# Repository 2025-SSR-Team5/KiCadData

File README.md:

# KiCadData

## Control Circuit<br>
- A面<br>
<br>

- B面<br>

連結した図
<br>

## Emergency Circuit<br>
動作電圧：7.8V以上（実測値）

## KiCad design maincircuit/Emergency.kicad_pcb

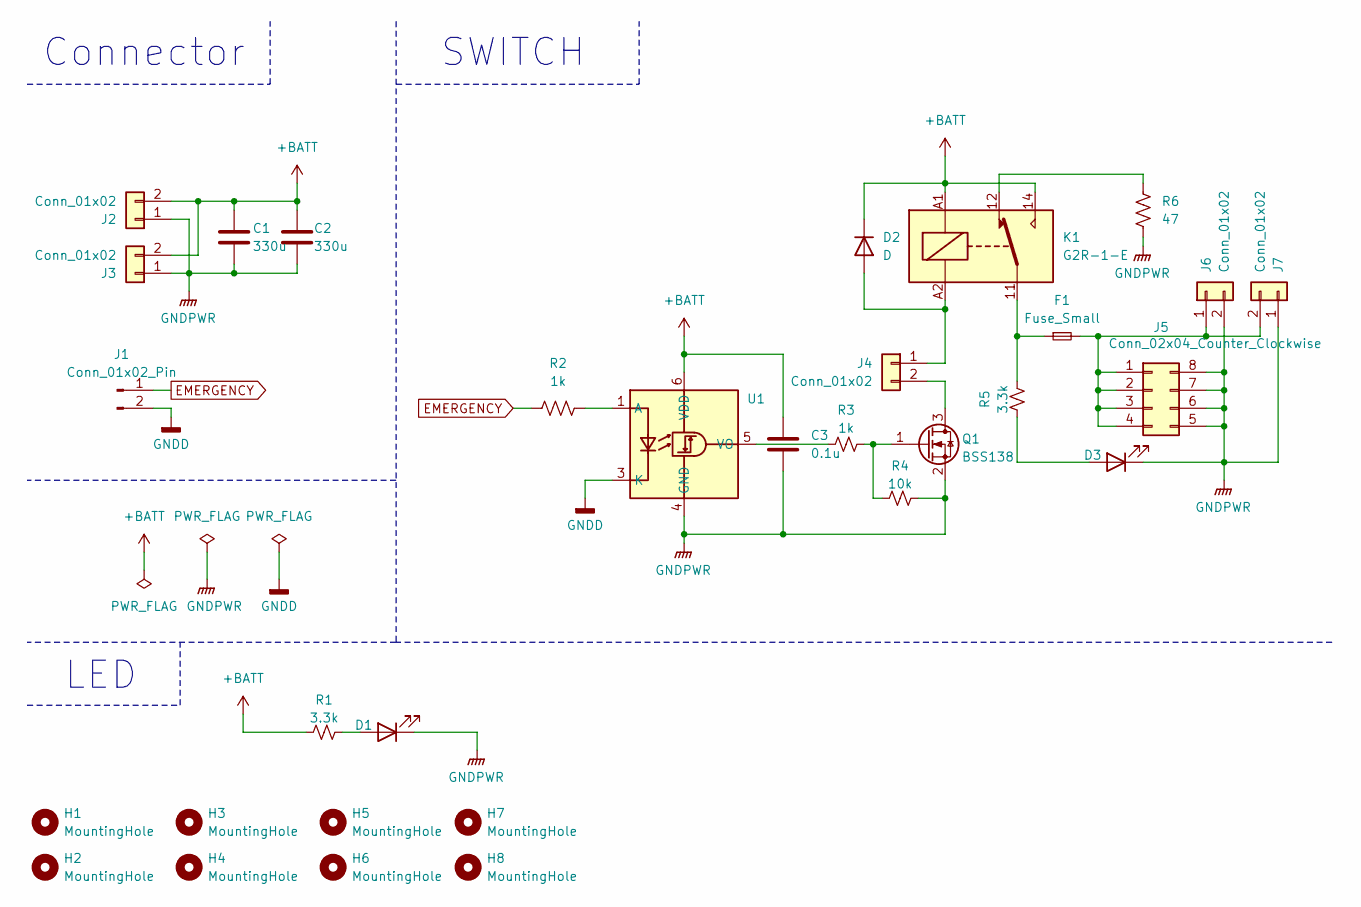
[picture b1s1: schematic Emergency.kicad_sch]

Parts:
C1, C2: 330u; CP_Elec_10x10
C3: 0.1u; C_0603_1608Metric_Pad1.08x0.95mm_HandSolder
D1, D3: LED; LED_0603_1608Metric
D2: D; D_DO-201AD_P15.24mm_Horizontal
F1: Fuse_Small; FUC-04
H1, H2, H3, H4, H5, H6, H7, H8: MountingHole; MountingHole_3.2mm_M3
J1: Conn_01x02_Pin; PinSocket_1x02_P2.54mm_Vertical
J2: Conn_01x02; AMASS_XT60PW-M_1x02_P7.20mm_Horizontal
J3, J7: Conn_01x02; AMASS_XT60PW-F_1x02_P7.20mm_Horizontal
J4, J6: Conn_01x02; JST_XH_B2B-XH-A_1x02_P2.50mm_Vertical
J5: Conn_02x04_Counter_Clockwise; PinSocket_2x04_P2.54mm_Vertical
K1: G2R-1-E
Q1: BSS138; SOT-23
R1, R5: 3.3k; R_0603_1608Metric_Pad0.98x0.95mm_HandSolder
R2, R3: 1k; R_0603_1608Metric_Pad0.98x0.95mm_HandSolder
R4: 10k; R_0603_1608Metric_Pad0.98x0.95mm_HandSolder
R6: 47; R_Axial_DIN0614_L14.3mm_D5.7mm_P20.32mm_Horizontal
U1: SO-5-6_4.55x3.7mm_P1.27mm

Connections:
+BATT: C1.1, C2.1, C3.1, D2.1 (K), J2.2, J3.2, K1.14, K1.A1, R1.1, U1.6 (VDD)
EMERGENCY: J1.1, R2.1
GNDD: J1.2, U1.3 (K)
GNDPWR: C1.2, C2.2, C3.2, D1.1 (K), D3.1 (K), J2.1, J3.1, J5.5, J5.6, J5.7, J5.8, J6.2, J7.1, Q1.2 (S), R4.2, R6.2, U1.4 (GND)
unnamed: D1.2 (A), R1.2
unnamed: D2.2 (A), J4.1, K1.A2
unnamed: D3.2 (A), R5.1
unnamed: F1.1, K1.11, R5.2
unnamed: J4.2, Q1.3 (D)
unnamed: F1.2, J5.1, J5.2, J5.3, J5.4, J6.1, J7.2
unnamed: K1.12, R6.1
unnamed: Q1.1 (G), R3.2, R4.1
unnamed: R2.2, U1.1 (A)
unnamed: R3.1, U1.5 (VO)

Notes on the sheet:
Connector
SWITCH
LED

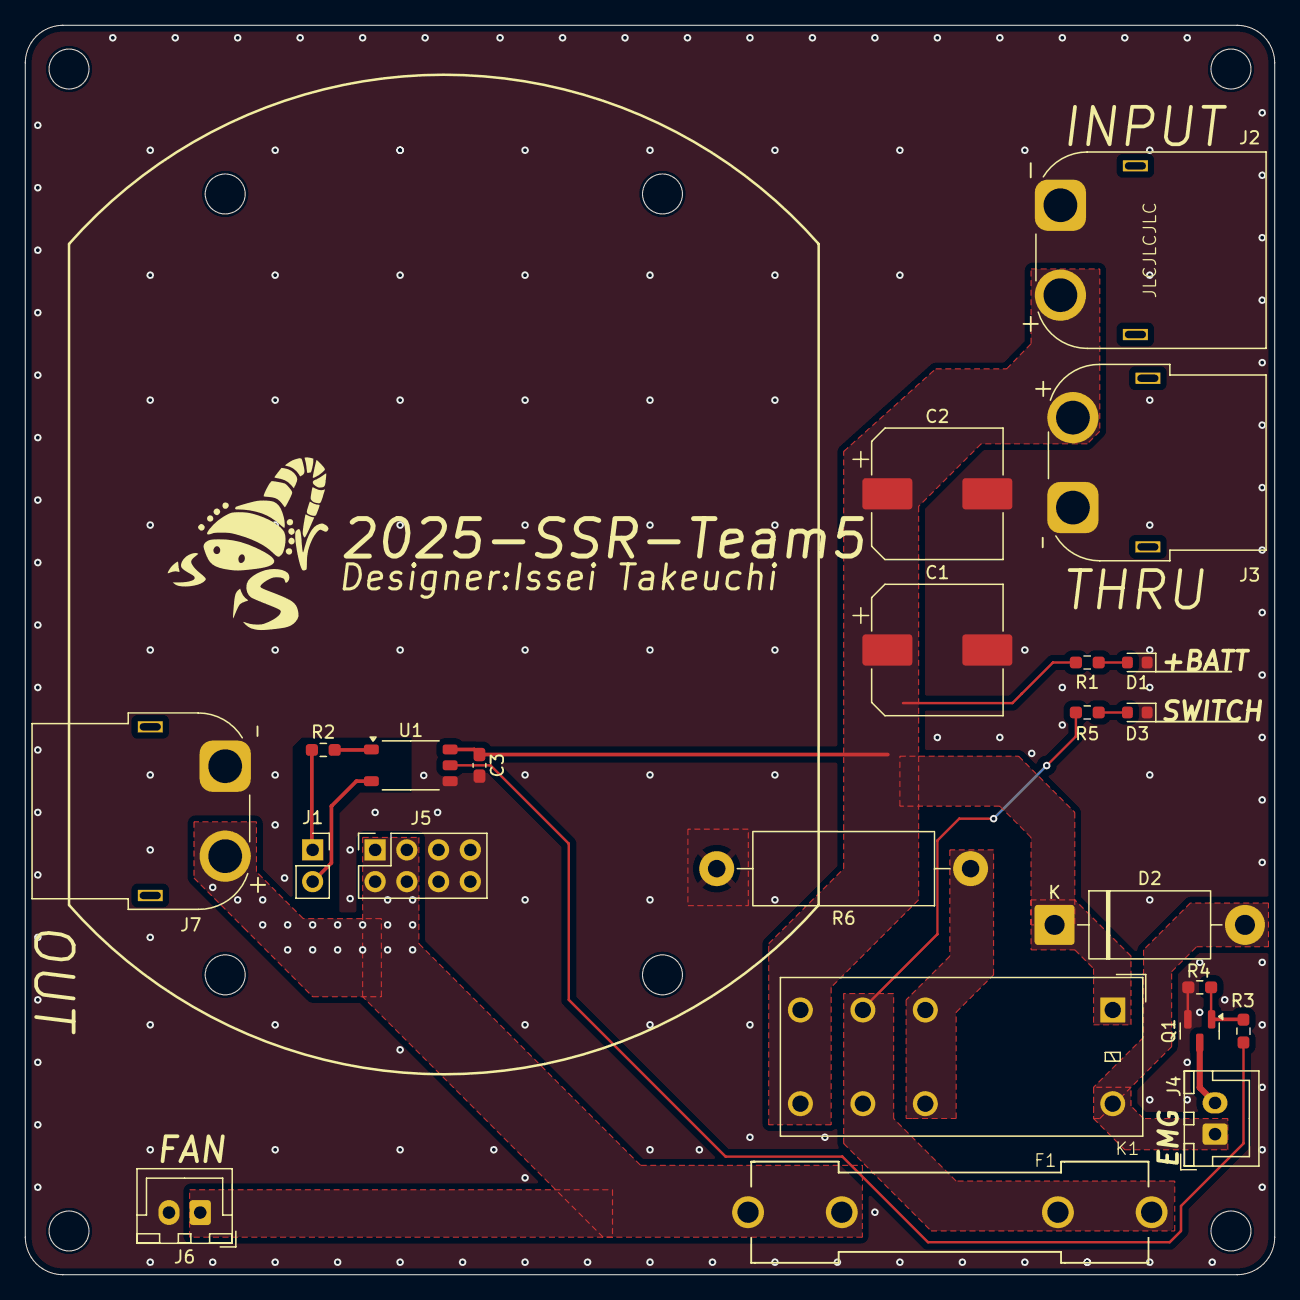
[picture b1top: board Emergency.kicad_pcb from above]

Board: 2 copper layers, 100.0 x 100.0 mm, 31 parts (0 on the bottom side), 14 nets.

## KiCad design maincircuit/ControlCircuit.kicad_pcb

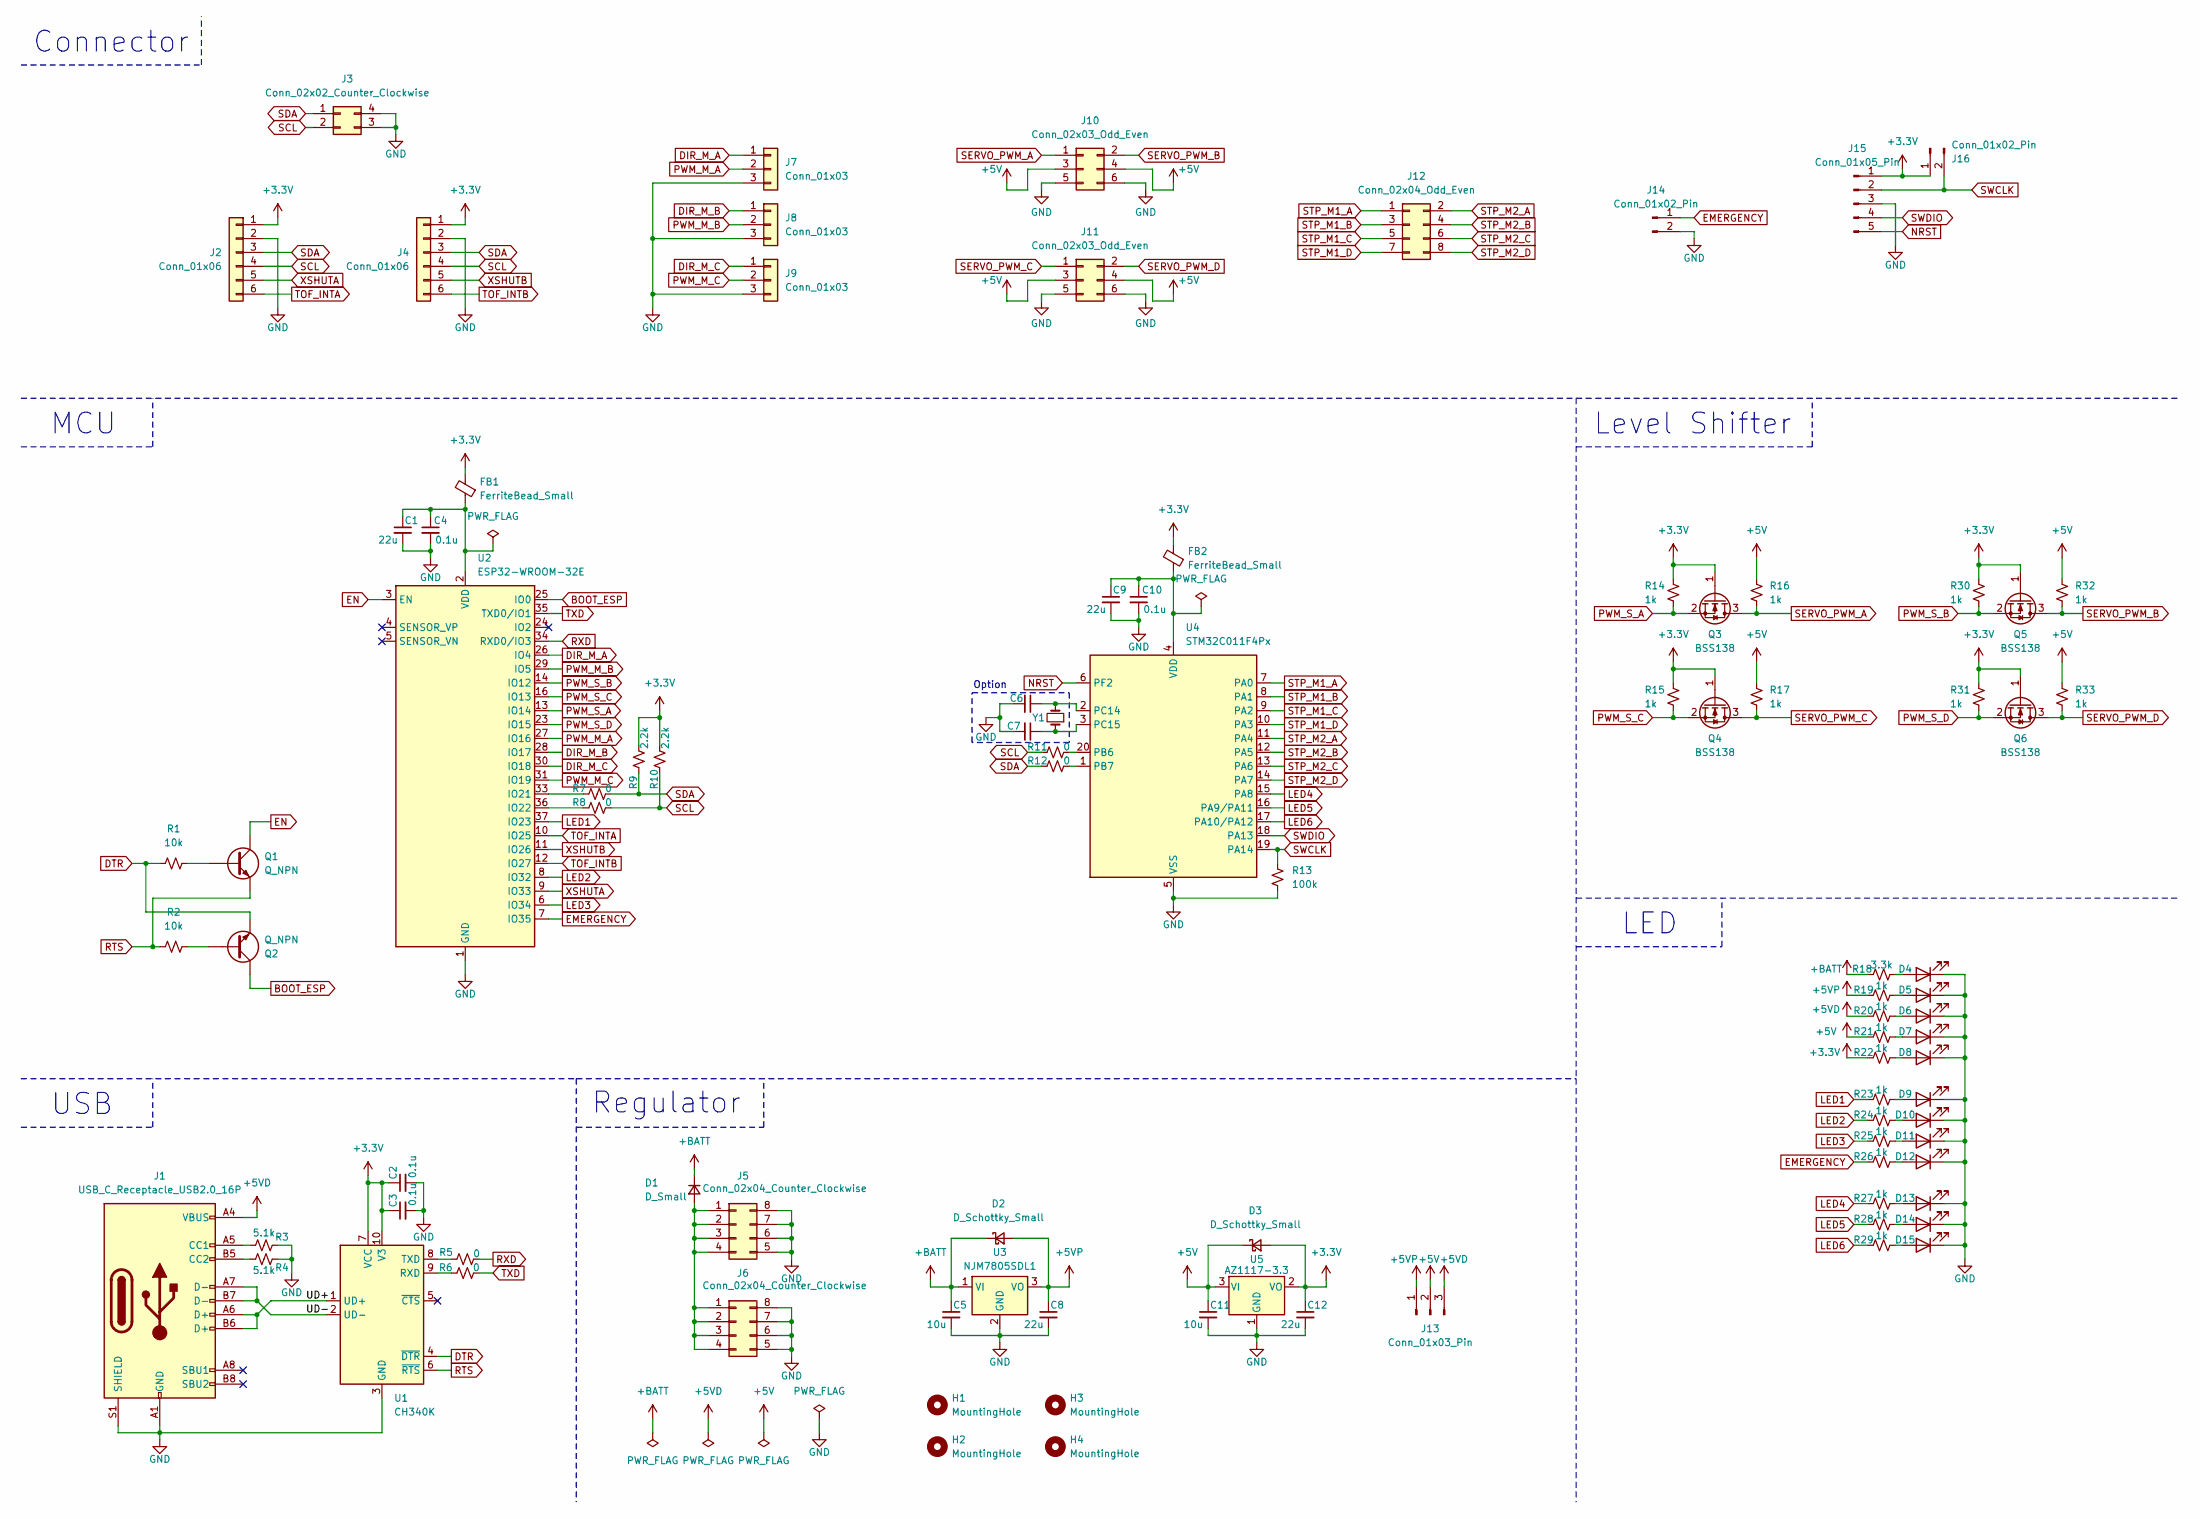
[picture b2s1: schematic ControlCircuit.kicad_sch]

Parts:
C1, C8, C9, C12: 22u; C_0603_1608Metric_Pad1.08x0.95mm_HandSolder
C2, C3, C4, C10: 0.1u; C_0603_1608Metric_Pad1.08x0.95mm_HandSolder
C5, C11: 10u; C_0603_1608Metric_Pad1.08x0.95mm_HandSolder
C6, C7: C_Small; C_0603_1608Metric_Pad1.08x0.95mm_HandSolder
D1: D_Small; Vishay_SMPA
D2, D3: D_Schottky_Small; Nexperia_CFP3_SOD-123W
D4, D5, D6, D7, D8, D9, D10, D11, D12, D13, D14, D15: LED; LED_0603_1608Metric
FB1, FB2: FerriteBead_Small; L_0603_1608Metric_Pad1.05x0.95mm_HandSolder
H1, H2, H3, H4: MountingHole; MountingHole_3.2mm_M3
J1: USB_C_Receptacle_USB2.0_16P; 5077CR-16-SMC2-BK-TR
J2, J4: Conn_01x06; JST_ZH_B6B-ZR_1x06_P1.50mm_Vertical
J3: Conn_02x02_Counter_Clockwise; PinSocket_2x02_P2.54mm_Vertical
J5: Conn_02x04_Counter_Clockwise; PinHeader_2x04_P2.54mm_Vertical
J6: Conn_02x04_Counter_Clockwise; PinSocket_2x04_P2.54mm_Vertical
J7, J8, J9: Conn_01x03; JST_XH_S3B-XH-A_1x03_P2.50mm_Horizontal
J10, J11: Conn_02x03_Odd_Even; PinHeader_2x03_P2.54mm_Horizontal
J12: Conn_02x04_Odd_Even; PinHeader_2x04_P2.54mm_Horizontal
J13: Conn_01x03_Pin; PinHeader_1x03_P2.54mm_Horizontal
J14: Conn_01x02_Pin; PinHeader_1x02_P2.54mm_Vertical
J15: Conn_01x05_Pin; PinHeader_1x05_P2.54mm_Horizontal
J16: Conn_01x02_Pin; PinHeader_1x02_P2.54mm_Horizontal
Q1, Q2: Q_NPN; SOT-23
Q3, Q4, Q5, Q6: BSS138; SOT-23
R1, R2: 10k; R_0603_1608Metric_Pad0.98x0.95mm_HandSolder
R3, R4: 5.1k; R_0603_1608Metric_Pad0.98x0.95mm_HandSolder
R5, R6, R7, R8, R11, R12: 0; R_0603_1608Metric_Pad0.98x0.95mm_HandSolder
R9, R10: 2.2k; R_0603_1608Metric_Pad0.98x0.95mm_HandSolder
R13: 100k; R_0603_1608Metric_Pad0.98x0.95mm_HandSolder
R14, R15, R16, R17, R19, R20, R21, R22, R23, R24, R25, R26, R27, R28, R29, R30, R31, R32, R33: 1k; R_0603_1608Metric_Pad0.98x0.95mm_HandSolder
R18: 3.3k; R_0603_1608Metric_Pad0.98x0.95mm_HandSolder
U1: CH340K; SSOP-10-1EP_3.9x4.9mm_P1mm_EP2.1x3.3mm
U2: ESP32-WROOM-32E; ESP32-WROOM-32D
U3: NJM7805SDL1; TO-252-2
U4: STM32C011F4Px; TSSOP-20_4.4x6.5mm_P0.65mm
U5: AZ1117-3.3; SOT-223
Y1: Crystal_Small; Crystal_SMD_3215-2Pin_3.2x1.5mm

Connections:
+3.3V: C2.1, C3.1, C12.1, D3.2 (A), FB1.2, FB2.2, J4.1, J15.1, J16.1, Q3.1 (G), Q4.1 (G), Q5.1 (G), Q6.1 (G), R9.1, R10.1, R14.1, R15.1, R22.1, R30.1, R31.1, U1.7 (VCC), U1.10 (V3), U5.2 (VO), U5.4 (VO2); also elsewhere on the board
+5V: C11.1, D3.1 (K), J10.3, J10.4, J11.3, J11.4, J13.2, R16.1, R17.1, R21.1, R32.1, R33.1, U5.3 (VI)
+5VD: J1.A4 (VBUS), J1.A9 (VBUS), J1.B4 (VBUS), J1.B9 (VBUS), J13.3, R20.1
+5VP: C8.1, D2.2 (A), J13.1, R19.1, U3.3 (VO)
+BATT: C5.1, D1.1 (K), D2.1 (K), R18.1, U3.1 (VI)
/UD+: J1.A6 (D+), J1.B6 (D+), U1.1 (UD+)
/UD-: J1.A7 (D-), J1.B7 (D-), U1.2 (UD-)
BOOT_ESP: Q2.3 (C), U2.25 (IO0)
DIR_M_A: J7.1, U2.26 (IO4)
DIR_M_B: J8.1, U2.28 (IO17)
DIR_M_C: J9.1, U2.30 (IO18)
DTR: Q2.2 (E), R1.1, U1.4 (~DTR)
EMERGENCY: J14.1, R26.1, U2.7 (IO35)
EN: Q1.3 (C), U2.3 (EN)
GND: C1.2, C2.2, C3.2, C4.2, C5.2, C6.2, C7.2, C8.2, C9.2, C10.2, C11.2, C12.2, D4.1 (K), D5.1 (K), D6.1 (K), D7.1 (K), D8.1 (K), D9.1 (K), D10.1 (K), D11.1 (K), D12.1 (K), D13.1 (K), D14.1 (K), D15.1 (K), J1.A1 (GND), J1.A12 (GND), J1.B1 (GND), J1.B12 (GND), J1.S1 (SHIELD), J3.3, J3.4, J4.2, J5.5, J5.6, J5.7, J5.8, J6.5, J6.6, J6.7, J6.8, J7.3, J8.3, J9.3, J10.5, J10.6, J11.5, J11.6, J14.2, J15.3, R3.2, R4.2, R13.2, U1.3 (GND), U1.11 (GND), U2.1 (GND), U2.15 (GND), U2.38 (GND), U2.39 (GND), U3.2 (GND), U4.5 (VSS), U5.1 (GND); also elsewhere on the board
LED1: R23.1, U2.37 (IO23)
LED2: R24.1, U2.8 (IO32)
LED3: R25.1, U2.6 (IO34)
LED4: R27.1, U4.15 (PA8)
LED5: R28.1, U4.16 (PA9/PA11)
LED6: R29.1, U4.17 (PA10/PA12)
NRST: J15.5, U4.6 (PF2)
unnamed: D1.2 (A), J5.1, J5.2, J5.3, J5.4, J6.1, J6.2, J6.3, J6.4
unnamed: D4.2 (A), R18.2
unnamed: D5.2 (A), R19.2
unnamed: D6.2 (A), R20.2
unnamed: D7.2 (A), R21.2
unnamed: D8.2 (A), R22.2
unnamed: D9.2 (A), R23.2
unnamed: D10.2 (A), R24.2
unnamed: D11.2 (A), R25.2
unnamed: D12.2 (A), R26.2
unnamed: D13.2 (A), R27.2
unnamed: D14.2 (A), R28.2
unnamed: D15.2 (A), R29.2
unnamed: J1.A5 (CC1), R3.1
unnamed: J1.B5 (CC2), R4.1
unnamed: Q1.1 (B), R1.2
unnamed: Q2.1 (B), R2.2
unnamed: R6.1, U1.9 (RXD)
unnamed: R5.1, U1.8 (TXD)
unnamed: R7.1, U2.33 (IO21)
unnamed: R8.1, U2.36 (IO22)
unnamed: C1.1, C4.1, FB1.1, U2.2 (VDD)
unnamed: R11.2, U4.20 (PB6)
unnamed: R12.2, U4.1 (PB7)
unnamed: C6.1, U4.2 (PC14), Y1.2
unnamed: C7.1, U4.3 (PC15), Y1.1
unnamed: C9.1, C10.1, FB2.1, U4.4 (VDD)
PWM_M_A: J7.2, U2.27 (IO16)
PWM_M_B: J8.2, U2.29 (IO5)
PWM_M_C: J9.2, U2.31 (IO19)
PWM_S_A: Q3.2 (S), R14.2, U2.13 (IO14)
PWM_S_B: Q5.2 (S), R30.2, U2.14 (IO12)
PWM_S_C: Q4.2 (S), R15.2, U2.16 (IO13)
PWM_S_D: Q6.2 (S), R31.2, U2.23 (IO15)
RTS: Q1.2 (E), R2.1, U1.6 (~RTS)
RXD: R5.2, U2.34 (RXD0/IO3)
SCL: J3.2, J4.4, R8.2, R10.2, R11.1; also elsewhere on the board
SDA: J3.1, J4.3, R7.2, R9.2, R12.1; also elsewhere on the board
SERVO_PWM_A: J10.1, Q3.3 (D), R16.2
SERVO_PWM_B: J10.2, Q5.3 (D), R32.2
SERVO_PWM_C: J11.1, Q4.3 (D), R17.2
SERVO_PWM_D: J11.2, Q6.3 (D), R33.2
STP_M1_A: J12.1, U4.7 (PA0)
STP_M1_B: J12.3, U4.8 (PA1)
STP_M1_C: J12.5, U4.9 (PA2)
STP_M1_D: J12.7, U4.10 (PA3)
STP_M2_A: J12.2, U4.11 (PA4)
STP_M2_B: J12.4, U4.12 (PA5)
STP_M2_C: J12.6, U4.13 (PA6)
STP_M2_D: J12.8, U4.14 (PA7)
SWCLK: J15.2, J16.2, R13.1, U4.19 (PA14)
SWDIO: J15.4, U4.18 (PA13)
TOF_INTA: J2.6, U2.10 (IO25); also elsewhere on the board
TOF_INTB: J4.6, U2.12 (IO27)
TXD: R6.2, U2.35 (TXD0/IO1)
XSHUTA: J2.5, U2.9 (IO33); also elsewhere on the board
XSHUTB: J4.5, U2.11 (IO26)

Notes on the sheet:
USB
Regulator
MCU
LED
Level Shifter
Option
Connector

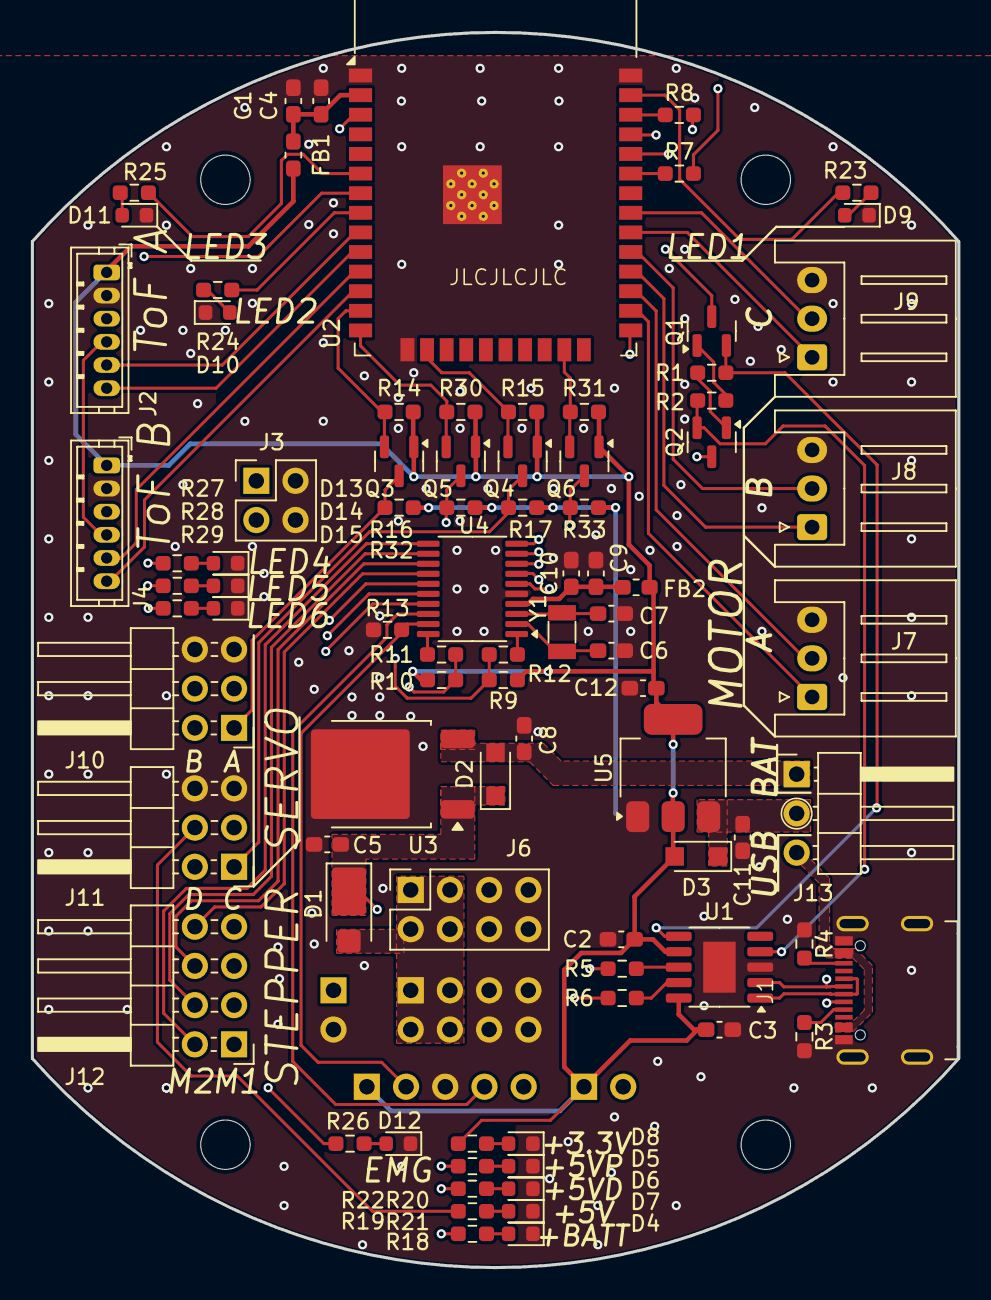
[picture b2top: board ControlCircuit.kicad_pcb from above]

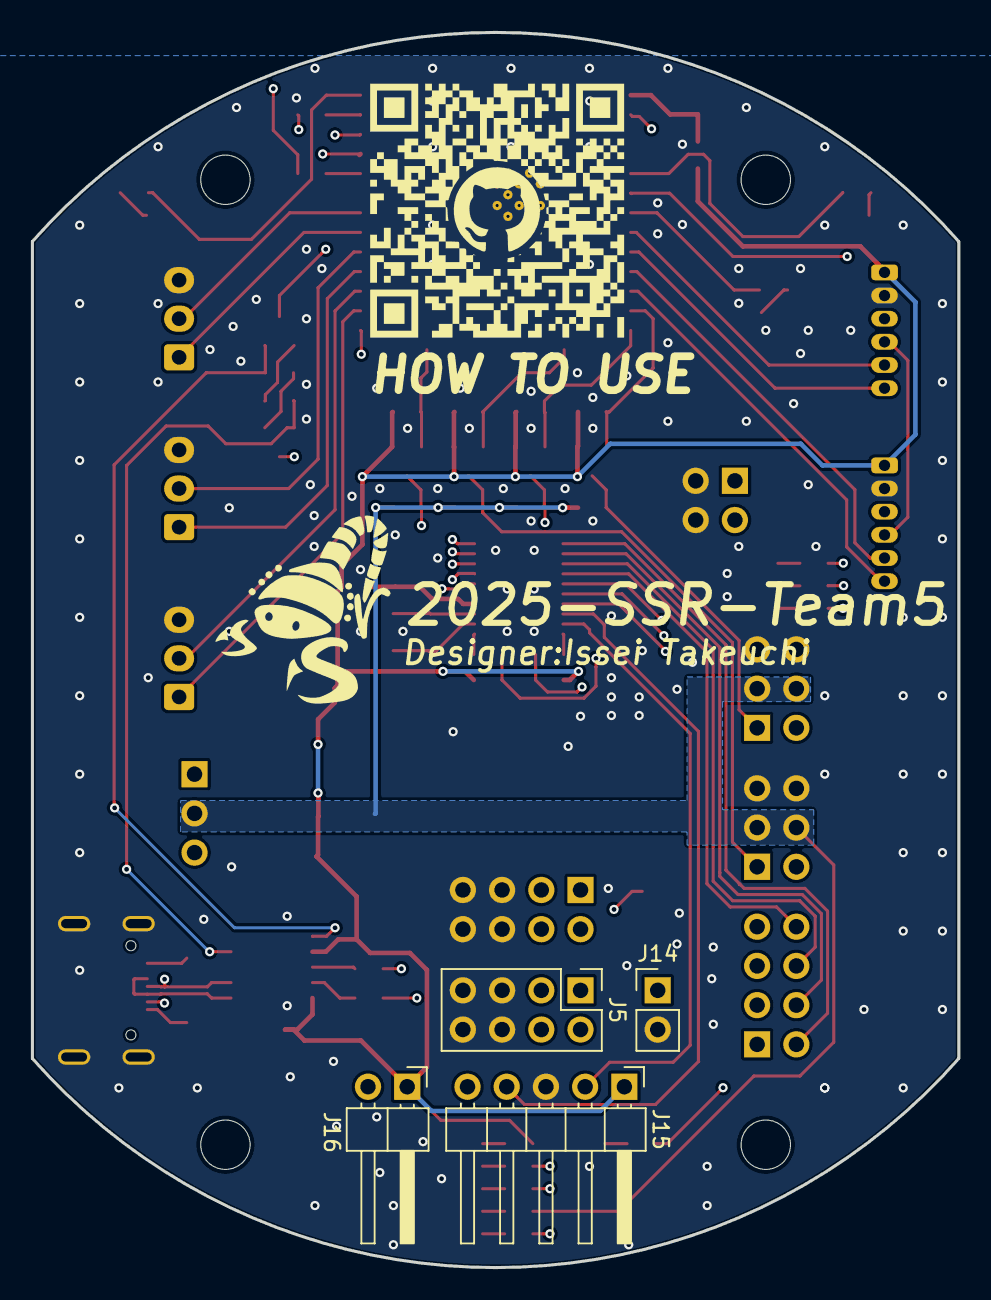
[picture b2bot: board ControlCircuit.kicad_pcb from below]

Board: 4 copper layers, 60.0 x 80.0 mm, 94 parts (4 on the bottom side), 79 nets.

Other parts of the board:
ToF A: Conn_01x06; JST_ZH_B6B-ZR_1x06_P1.50mm_Vertical

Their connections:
+3.3V: ToF A.1; also elsewhere on the board
GND: ToF A.2; also elsewhere on the board
SCL: ToF A.4; also elsewhere on the board
SDA: ToF A.3; also elsewhere on the board
TOF_INTA: ToF A.6; also elsewhere on the board
XSHUTA: ToF A.5; also elsewhere on the board

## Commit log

2025-06-30 add: initial commit/非常停止回路関係の追加
2025-07-07 add: ESP32-WROOM-32E-MINIのライブラリの追加
2025-07-13 add: 07/13進捗分(主にcontrol回路)
2025-08-02 [add]ControlCircuit完成
2025-08-05 add: ver1.0の基板データの完成
